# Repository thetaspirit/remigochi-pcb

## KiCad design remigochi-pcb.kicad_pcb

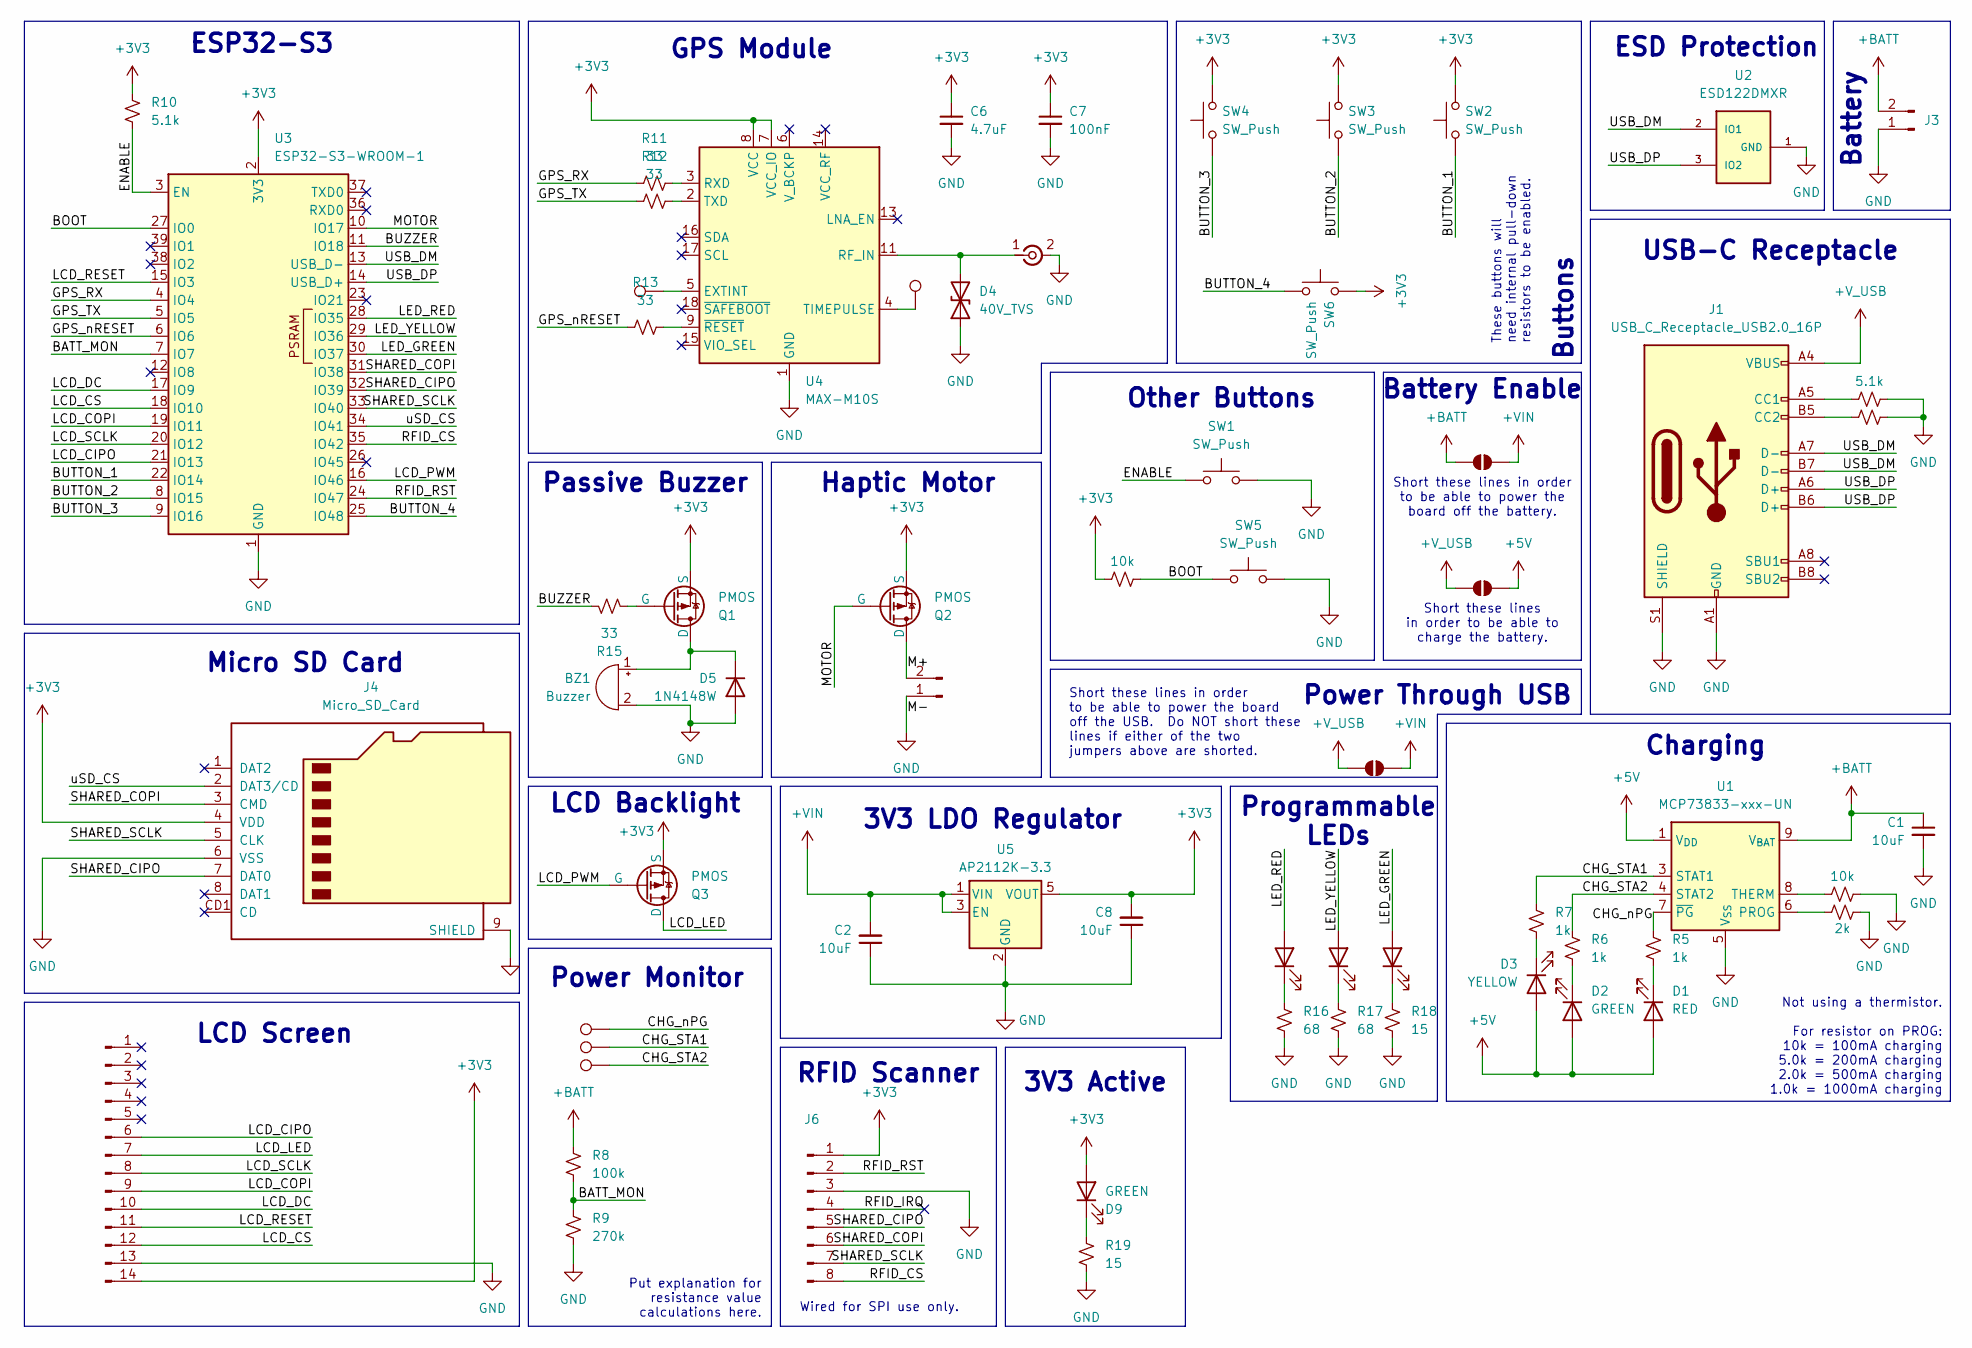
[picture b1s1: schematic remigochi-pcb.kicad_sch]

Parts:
BZ1: Buzzer; Huaneng MLT-7525; LCSC Part Number C95299
C1, C2, C8: 10uF; C_0603_1608Metric; LCSC Part Number C19702
C6: 4.7uF; C_0603_1608Metric; LCSC Part Number C19666
C7: 100nF; C_0603_1608Metric; LCSC Part Number C14663
D1, D8: RED; D_1206_3216Metric; LCSC Part Number C2984265
D2, D7, D9: GREEN; D_1206_3216Metric; LCSC Part Number C965825
D3, D6: YELLOW; D_1206_3216Metric; LCSC Part Number C1322289
D4: 40V_TVS; D_0402_1005Metric; LCSC Part Number C10662
D5: 1N4148W; D_SOD-123; LCSC Part Number C241939
J1: USB_C_Receptacle_USB2.0_16P; USB_C_Receptacle_G-Switch_GT-USB-7010ASV; LCSC Part Number C2988369
J2: Conn_01x02_Pin; PinHeader_1x02_P2.54mm_Vertical
J3: Conn_01x02_Pin; SolderWire-1.5sqmm_1x02_P6mm_D1.7mm_OD3mm_Relief
J4: Micro_SD_Card; TF-01A; LCSC Part Number C20613191
J5: Conn_Coaxial_Small; U.FL_Hirose_U.FL-R-SMT-1_Vertical; LCSC Part Number C88374
J6: Conn_01x08_Pin; PinHeader_1x08_P2.54mm_Vertical
J9: Conn_01x14_Pin; PinHeader_1x14_P2.54mm_Vertical
JP2, JP6, JP8: SolderJumper_2_Open; SolderJumper-2_P1.3mm_Open_RoundedPad1.0x1.5mm
Q1, Q2, Q3: PMOS; SOT-23; LCSC Part Number C10487
R1, R2, R10: 5.1k; R_0402_1005Metric; LCSC Part Number C105872
R3, R14: 10k; R_0402_1005Metric; LCSC Part Number C60490
R4: 2k; R_0402_1005Metric; LCSC Part Number C60488
R5, R6, R7: 1k; R_0402_1005Metric; LCSC Part Number C106235
R8: 100k; R_0402_1005Metric; LCSC Part Number C60491
R9: 270k; R_0402_1005Metric; LCSC Part Number C163475
R11, R12, R13, R15: 33; R_0402_1005Metric; LCSC Part Number C138002
R16, R17: 68; R_0402_1005Metric; LCSC Part Number C2909380
R18, R19: 15; R_0402_1005Metric; LCSC Part Number C138052
SW1, SW2, SW3, SW4, SW5, SW6: SW_Push; Korean Hroparts Elec K2-1157SP-I4SW-01; LCSC Part Number C2909692
TP1, TP2, TP7, TP8, TP9: TestPoint; TestPoint_Pad_D1.0mm
U1: MCP73833-xxx-UN; MSOP-10_3x3mm_P0.5mm; LCSC Part Number C627668
U2: ESD122DMXR; IC_ESD122DMXR; PARTREV A; LCSC Part Number C544474
U3: ESP32-S3-WROOM-1; LCSC Part Number C2913197
U4: MAX-M10S; ublox_MAX; LCSC Part Number C4153167
U5: AP2112K-3.3; SOT-23-5; LCSC Part Number C23380830

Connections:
+3V3: C6.1, C7.1, C8.2, D9.2 (A), J4.4 (VDD), J6.1, J9.14, Q1.2 (S), Q2.2 (S), Q3.2 (S), R10.1, R14.1, SW2.2, SW3.2, SW4.2, SW6.2, U3.2 (3V3), U4.7 (VCC_IO), U4.8 (VCC), U5.5 (VOUT)
+5V: D1.2 (A), D2.2 (A), D3.2 (A), JP2.2 (B), U1.1 (V_{DD}), U1.2 (V_{DD})
+BATT: C1.1, J3.2, JP6.1 (A), R8.1, U1.9 (V_{BAT}), U1.10 (V_{BAT})
+VIN: C2.2, JP6.2 (B), JP8.2 (B), U5.1 (VIN), U5.3 (EN)
+V_USB: J1.A4 (VBUS), J1.A9 (VBUS), J1.B4 (VBUS), J1.B9 (VBUS), JP2.1 (A), JP8.1 (A)
/BATT_MON: R8.2, R9.1, U3.7 (IO7)
/BOOT: R14.2, SW5.1, U3.27 (IO0)
/BUTTON_1: SW2.1, U3.22 (IO14)
/BUTTON_2: SW3.1, U3.8 (IO15)
/BUTTON_3: SW4.1, U3.9 (IO16)
/BUTTON_4: SW6.1, U3.25 (IO48)
/BUZZER: R15.1, U3.11 (IO18)
/CHG_STA1: R7.1, TP8.1 (1_1), U1.3 (STAT1)
/CHG_STA2: R6.2, TP9.1 (1_1), U1.4 (STAT2)
/CHG_nPG: R5.2, TP7.1 (1_1), U1.7 (~PG)
/ENABLE: R10.2, SW1.1, U3.3 (EN)
/GPS_RX: R11.1, U3.4 (IO4)
/GPS_TX: R12.1, U3.5 (IO5)
/GPS_nRESET: R13.1, U3.6 (IO6)
/LCD_CIPO: J9.6, U3.21 (IO13)
/LCD_COPI: J9.9, U3.19 (IO11)
/LCD_CS: J9.12, U3.18 (IO10)
/LCD_DC: J9.10, U3.17 (IO9)
/LCD_LED: J9.7, Q3.3 (D)
/LCD_PWM: Q3.1 (G), U3.16 (IO46)
/LCD_RESET: J9.11, U3.15 (IO3)
/LCD_SCLK: J9.8, U3.20 (IO12)
/LED_GREEN: D7.2 (A), U3.30 (IO37)
/LED_RED: D8.2 (A), U3.28 (IO35)
/LED_YELLOW: D6.2 (A), U3.29 (IO36)
/M+: J2.2, Q2.3 (D)
/MOTOR: Q2.1 (G), U3.10 (IO17)
/RFID_CS: J6.8, U3.35 (IO42)
/RFID_IRQ: J6.4
/RFID_RST: J6.2, U3.24 (IO47)
/SHARED_CIPO: J4.7 (DAT0), J6.5, U3.32 (IO39)
/SHARED_COPI: J4.3 (CMD), J6.6, U3.31 (IO38)
/SHARED_SCLK: J4.5 (CLK), J6.7, U3.33 (IO40)
/USB_DM: J1.A7 (D-), J1.B7 (D-), U2.2 (IO1), U3.13 (USB_D-)
/USB_DP: J1.A6 (D+), J1.B6 (D+), U2.3 (IO2), U3.14 (USB_D+)
/uSD_CS: J4.2 (DAT3/CD), U3.34 (IO41)
GND: BZ1.2 (-), C1.2, C2.1, C6.2, C7.2, C8.1, D4.1 (A1), D5.2 (A), J1.A1 (GND), J1.A12 (GND), J1.B1 (GND), J1.B12 (GND), J1.S1 (SHIELD), J2.1, J3.1, J4.6 (VSS), J4.9 (SHIELD), J5.2 (Ext), J6.3, J9.13, R1.2, R2.2, R3.2, R4.2, R9.2, R16.2, R17.2, R18.2, R19.2, SW1.2, SW5.2, U1.5 (V_{SS}), U2.1 (GND), U3.1 (GND), U3.40 (GND), U3.41 (GND), U4.1 (GND), U4.10 (GND), U4.12 (GND), U5.2 (GND)
unnamed: BZ1.1 (+), D5.1 (K), Q1.3 (D)
unnamed: D1.1 (K), R5.1
unnamed: D2.1 (K), R6.1
unnamed: D3.1 (K), R7.2
unnamed: D4.2 (A2), J5.1 (In), U4.11 (RF_IN)
unnamed: D6.1 (K), R17.1
unnamed: D7.1 (K), R18.1
unnamed: D8.1 (K), R16.1
unnamed: D9.1 (K), R19.1
unnamed: J1.A5 (CC1), R1.1
unnamed: J1.B5 (CC2), R2.1
unnamed: Q1.1 (G), R15.2
unnamed: R4.1, U1.6 (PROG)
unnamed: R3.1, U1.8 (THERM)
unnamed: TP1.1 (1_1), U4.5 (EXTINT)
unnamed: R11.2, U4.3 (RXD)
unnamed: TP2.1 (1_1), U4.4 (TIMEPULSE)
unnamed: R12.2, U4.2 (TXD)
unnamed: R13.2, U4.9 (~RESET)

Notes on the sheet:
Other Buttons
Passive Buzzer
USB-C Receptacle
ESD Protection
Programmable LEDs
Short these lines in order to be able to charge the battery.
These buttons will need internal pull-down resistors to be enabled.
Charging
LCD Backlight
Buttons
RFID Scanner
ESP32-S3
3V3 LDO Regulator
Power Monitor
Short these lines in order to be able to power the board off the USB. Do NOT short these lines if either of the two jumpers above are shorted.
3V3 Active
Not using a thermistor. For resistor on PROG: 10k = 100mA charging 5.0k = 200mA charging 2.0k = 500mA charging 1.0k = 1000mA charging
Power Through USB
Micro SD Card
Battery
Put explanation for resistance value calculations here.
Haptic Motor
Battery Enable
LCD Screen
Short these lines in order to be able to power the board off the battery.
Wired for SPI use only.
GPS Module

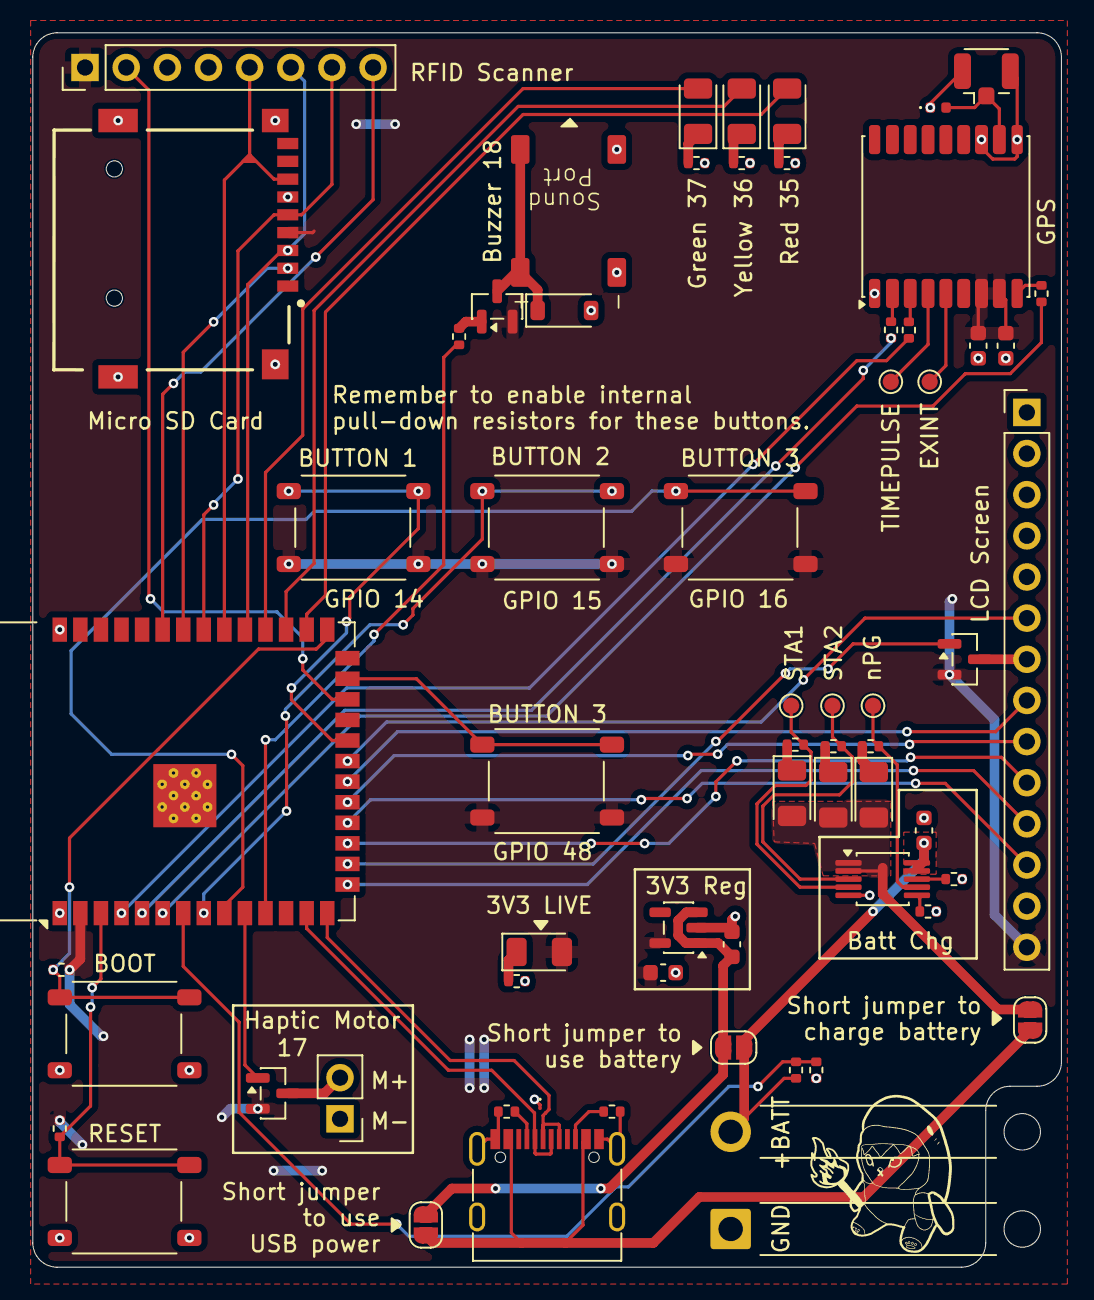
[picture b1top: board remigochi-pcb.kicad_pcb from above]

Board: 2 copper layers, 63.5 x 76.2 mm, 63 parts (0 on the bottom side), 60 nets.

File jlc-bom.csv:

Comment,Designator,LCSC Part Number,Footprint
Buzzer,BZ1,C95299,buzzer:Huaneng MLT-7525
4.7uF,C6,C19666,Capacitor_SMD:C_0603_1608Metric
100nF,C7,C14663,Capacitor_SMD:C_0603_1608Metric
40V_TVS,D4,C10662,Diode_SMD:D_0402_1005Metric
1N4148W,D5,C241939,Diode_SMD:D_SOD-123
USB_C_Receptacle_USB2.0_16P,J1,C2988369,Connector_USB:USB_C_Receptacle_G-Switch_GT-USB-7010ASV
Micro_SD_Card,J4,C20613191,microSD-Card:TF-01A
Conn_Coaxial_Small,J5,C88374,Connector_Coaxial:U.FL_Hirose_U.FL-R-SMT-1_Vertical
2k,R4,C60488,Resistor_SMD:R_0402_1005Metric
100k,R8,C60491,Resistor_SMD:R_0402_1005Metric
270k,R9,C163475,Resistor_SMD:R_0402_1005Metric
MCP73833-xxx-UN,U1,C627668,Package_SO:MSOP-10_3x3mm_P0.5mm
ESD122DMXR,U2,C544474,esd:IC_ESD122DMXR
ESP32-S3-WROOM-1,U3,C2913197,RF_Module:ESP32-S3-WROOM-1
MAX-M10S,U4,C4153167,RF_GPS:ublox_MAX
AP2112K-3.3,U5,C23380830,Package_TO_SOT_SMD:SOT-23-5
RED,"D1,D8",C2984265,Diode_SMD:D_1206_3216Metric
YELLOW,"D3,D6",C1322289,Diode_SMD:D_1206_3216Metric
10k,"R3,R14",C60490,Resistor_SMD:R_0402_1005Metric
68,"R16,R17",C2909380,Resistor_SMD:R_0402_1005Metric
15,"R18,R19",C138052,Resistor_SMD:R_0402_1005Metric
10uF,"C1,C2,C8",C19702,Capacitor_SMD:C_0603_1608Metric
GREEN,"D2,D7,D9",C965825,Diode_SMD:D_1206_3216Metric
PMOS,"Q1,Q2,Q3",C10487,Package_TO_SOT_SMD:SOT-23
5.1k,"R1,R2,R10",C105872,Resistor_SMD:R_0402_1005Metric
1k,"R5,R6,R7",C106235,Resistor_SMD:R_0402_1005Metric
33,"R11,R12,R13,R15",C138002,Resistor_SMD:R_0402_1005Metric
SW_Push,"SW1,SW2,SW3,SW4,SW5,SW6",C2909692,push-button:Korean Hroparts Elec K2-1157SP-I4SW-01

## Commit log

2026-02-12 added battery and USB circuitry
2026-02-14 added esp32 and some other stuff to schematic
2026-02-16 added microSD card to schematic. wip gps
    added fp-info-cache to ignore.
2026-02-18 added buzzer and motor, modified GPS
    GPS still needs modifications, still have a few more subsystems to add
    to pcb
2026-02-19 redid SPI pins, started adding breakout pins
2026-02-19 added/rearranged missing GPIO pins
    added some of the footprints
2026-02-23 added all footprints
    * passes ERC! (no errors, but some warnings)
    * schematic could possibly still need minor edits.
    * added custom footprint libraries.
    * added flyback diode to buzzer.
2026-02-23 changed TVS diode footprint (and actual part)
2026-02-23 WIP layout, started arranging stuff
2026-02-23 minor edits to schematic, WIP placement for layout
    * changed buck reg to LDO bc i finally decided the minimum input
    voltage on the buck was too high.
    * connected LCD_ENABLE pin to a gpio pin (oops)
    * placed stuff, almost done with placement, should start routing soon.
2026-02-24 layout done
    added LCSC numbers to bom
    still need to do silkscreen
2026-02-24 layout actually passes DRC now lol
    WIP silkscreens
2026-02-25 finished silkscreen
2026-02-25 fixed 3v3 planes being disconnected
2026-02-25 added manufacturing and assembly files
    placed our first order!!!
2026-03-31 deleted manufacturing files in root directory
2026-04-01 added .history to gitignore
2026-04-01 changed nmos to pmos, added power config jumpers
2026-04-01 added ESD to the USB, removed jumpers
2026-04-01 added led indicating battery connected
2026-04-02 WIP layout
2026-04-03 fix: connected RFID to CS pin
    renamed some lines
2026-04-03 placement mostly done
2026-04-04 placement and board shape done
    ready for routing
2026-04-05 routing mostly done, saving as checkpoint
    for some reason the nets/connections are fucked up somehow.
    might redo layout completely cuz idk how that happened.
2026-04-05 layout done, drc passes
    prepare BOM then send to JLC
2026-04-06 rev 2 sent off for manufacturing and assembly.
2026-04-17 idk what these changes are
